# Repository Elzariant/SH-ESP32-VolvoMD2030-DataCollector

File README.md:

# SH-ESP32 Volvo Penta 2030 - Data Collector

Volvo Penta MD series do not implement any CAN-BUS.
This work is built on several projects.

I thank frankly Mat from "Boating with the Baileys" channel who has been the main source of inspiration (and code ;-) ).

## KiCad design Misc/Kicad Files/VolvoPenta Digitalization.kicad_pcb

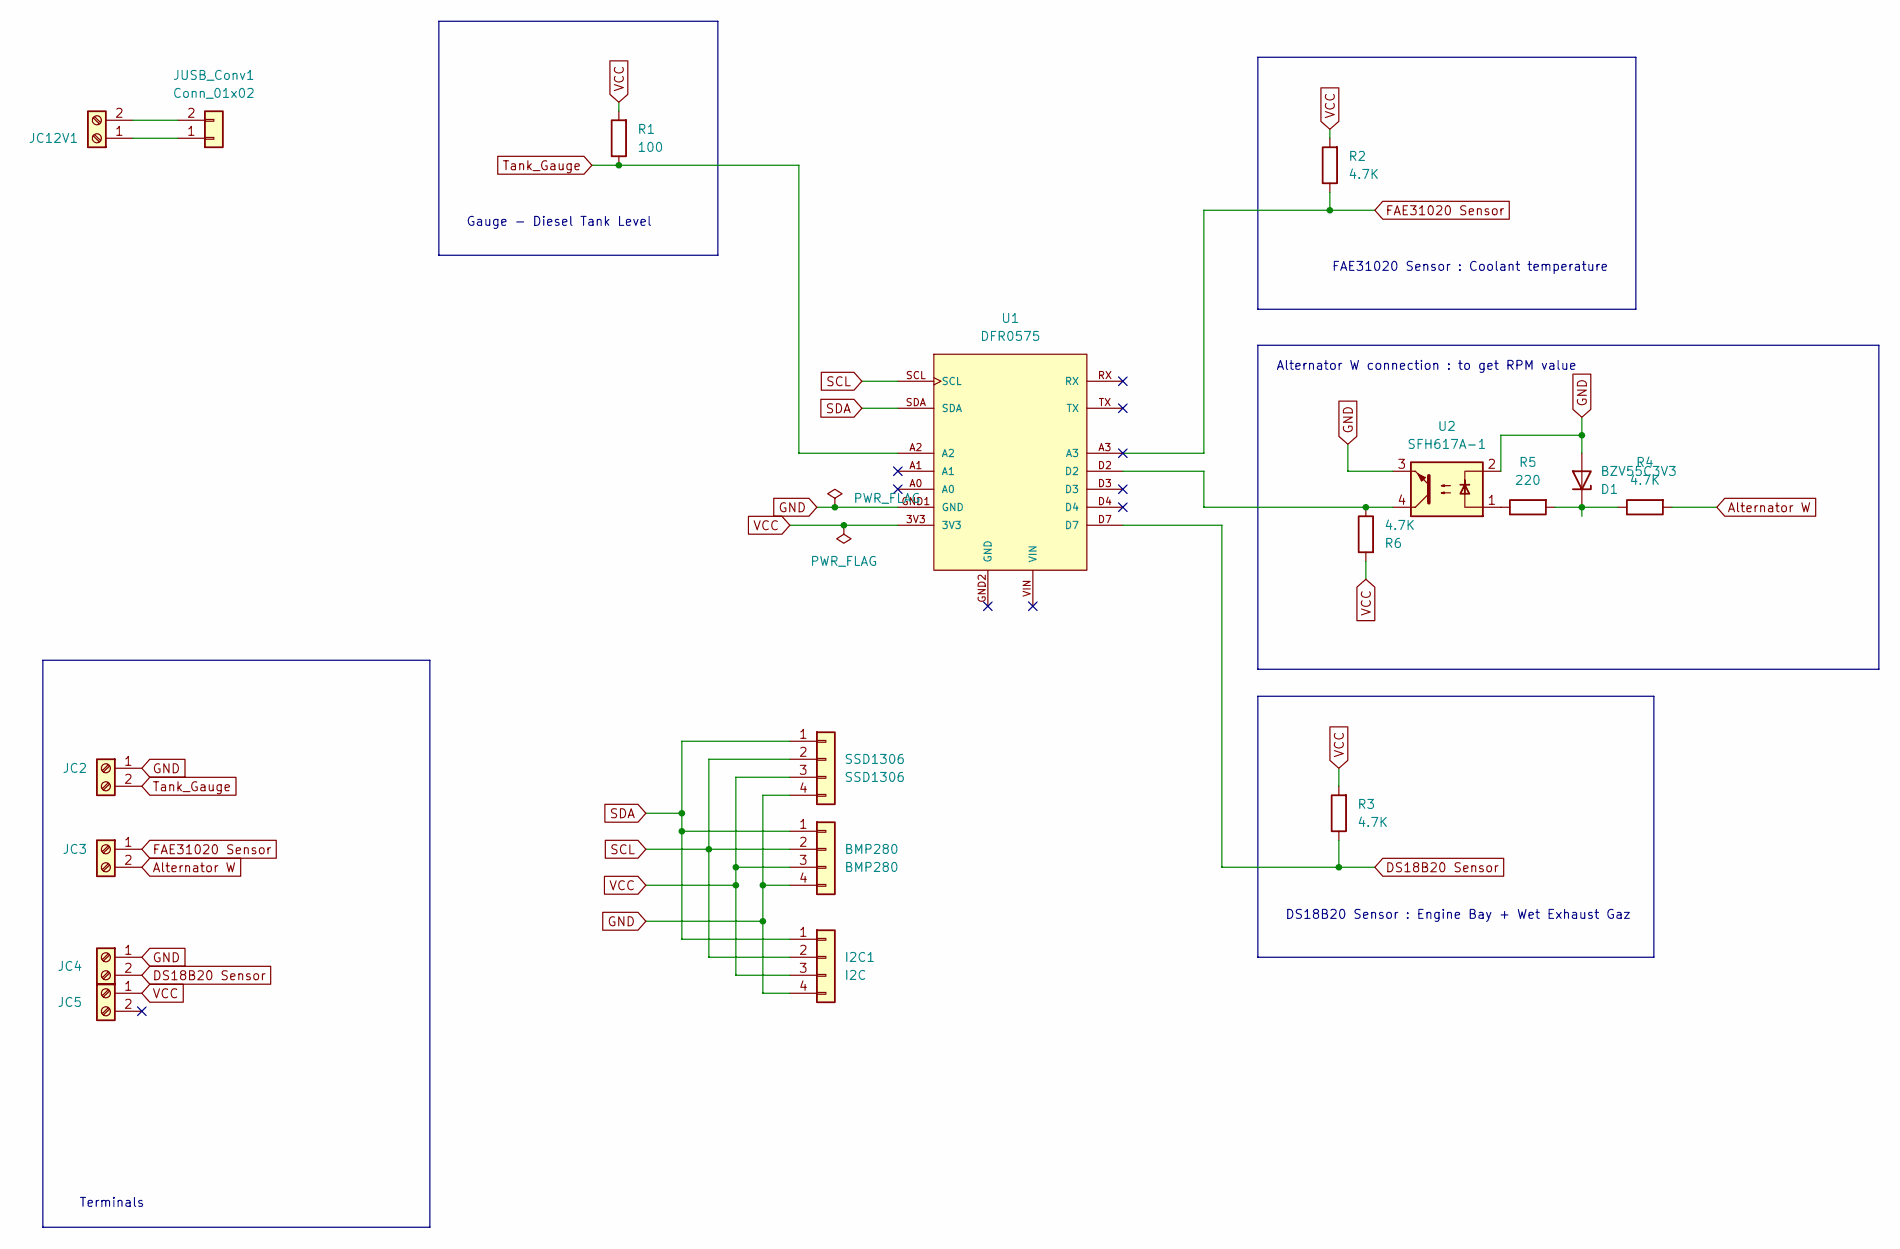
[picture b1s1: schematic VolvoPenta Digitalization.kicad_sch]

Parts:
BMP280: BMP280; PinHeader_1x04_P2.54mm_Vertical
D1: BZV55C3V3; D_DO-35_SOD27_P7.62mm_Horizontal
I2C1: I2C; PinHeader_1x04_P2.54mm_Vertical
JC2, JC3, JC4, JC5, JC12V1: Screw_Terminal_01x02; TerminalBlock_bornier-2_P5.08mm
JUSB_Conv1: Conn_01x02; PinHeader_1x02_P2.54mm_Vertical
R1: 100; R_Axial_DIN0207_L6.3mm_D2.5mm_P7.62mm_Horizontal
R2, R3, R4, R6: 4.7K; R_Axial_DIN0207_L6.3mm_D2.5mm_P7.62mm_Horizontal
R5: 220; R_Axial_DIN0207_L6.3mm_D2.5mm_P7.62mm_Horizontal
SSD1306: SSD1306; PinHeader_1x04_P2.54mm_Vertical
U1: DFR0575; Beetle ESP32 (DFR0575)
U2: SFH617A-1; DIP-4_W7.62mm

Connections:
Alternator W: JC3.2, R4.2
DS18B20 Sensor: JC4.2, R3.1, U1.D7
FAE31020 Sensor: JC3.1, R2.1, U1.A3
GND: BMP280.4, D1.2 (A), I2C1.4, JC2.1, JC4.1, SSD1306.4, U1.GND1 (GND), U2.2, U2.3
unnamed: JC12V1.1, JUSB_Conv1.1
unnamed: JC12V1.2, JUSB_Conv1.2
unnamed: D1.1 (K), R4.1, R5.2
unnamed: R6.1, U1.D2, U2.4
unnamed: R5.1, U2.1
SCL: BMP280.2, I2C1.2, SSD1306.2, U1.SCL
SDA: BMP280.1, I2C1.1, SSD1306.1, U1.SDA
Tank_Gauge: JC2.2, R1.1, U1.A2
VCC: BMP280.3, I2C1.3, JC5.1, R1.2, R2.2, R3.2, R6.2, SSD1306.3, U1.3V3

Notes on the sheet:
Terminals
DS18B20 Sensor : Engine Bay + Wet Exhaust Gaz
FAE31020 Sensor : Coolant temperature
Alternator W connection : to get RPM value
Gauge - Diesel Tank Level

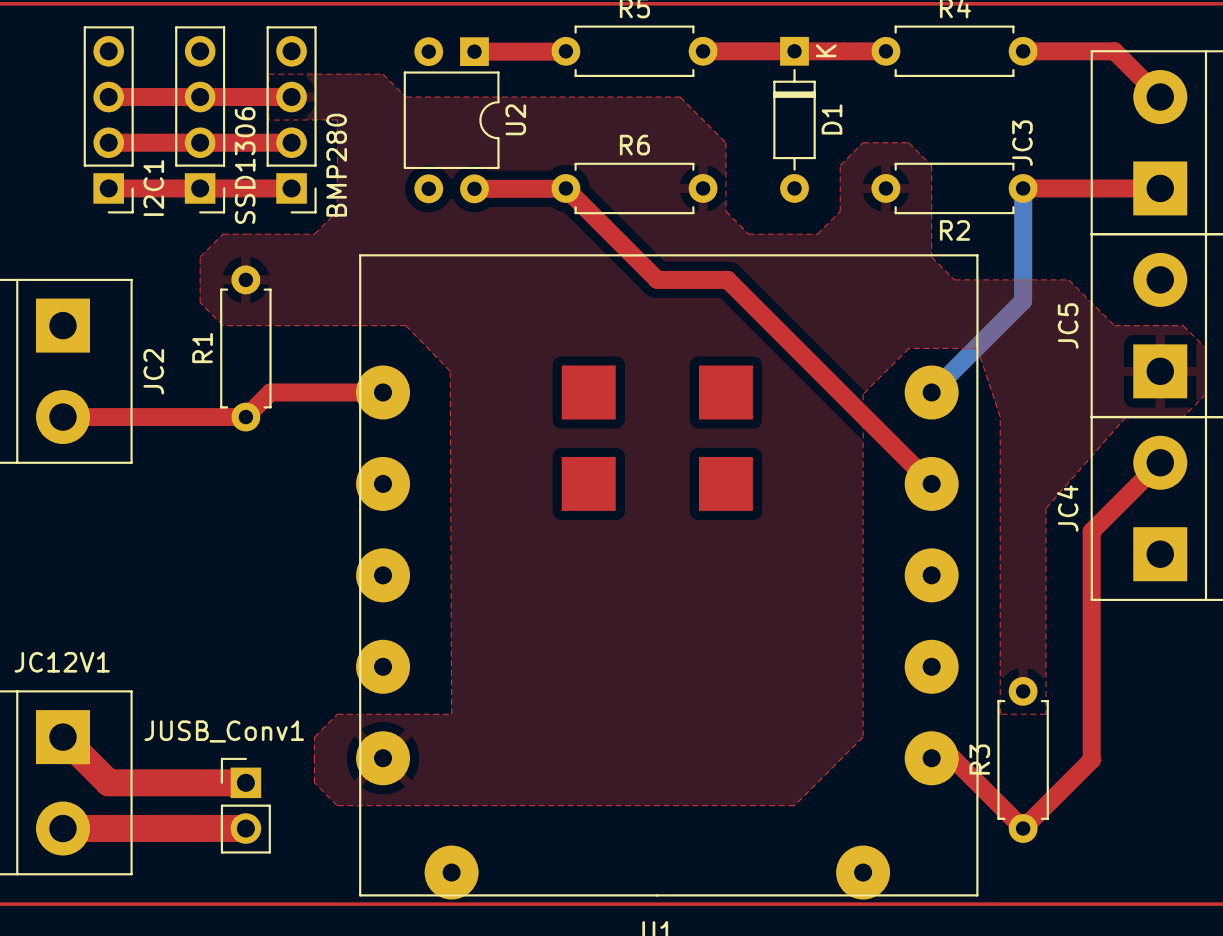
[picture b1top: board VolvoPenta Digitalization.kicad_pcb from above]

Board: 2 copper layers, 18 parts (0 on the bottom side), 13 nets.

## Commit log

2022-08-24 New Update
2022-08-24 Test~1
2022-09-20 Review layout
2022-09-20 Added misc files with schema
2022-09-23 Replaced FAE30210 sensor with DS18B20
2022-12-27 Work in progress : total capacity of diesel tank
2022-12-30 New rev
2023-02-04 Fuel Gauge : works now
2023-02-04 Added : board references
2023-02-04 Added Kicad files
